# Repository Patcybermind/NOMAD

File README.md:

# NOMAD
A laptop designed to be customisable, portable and open source

if you're in the hc slack make sure to join #pats-basement

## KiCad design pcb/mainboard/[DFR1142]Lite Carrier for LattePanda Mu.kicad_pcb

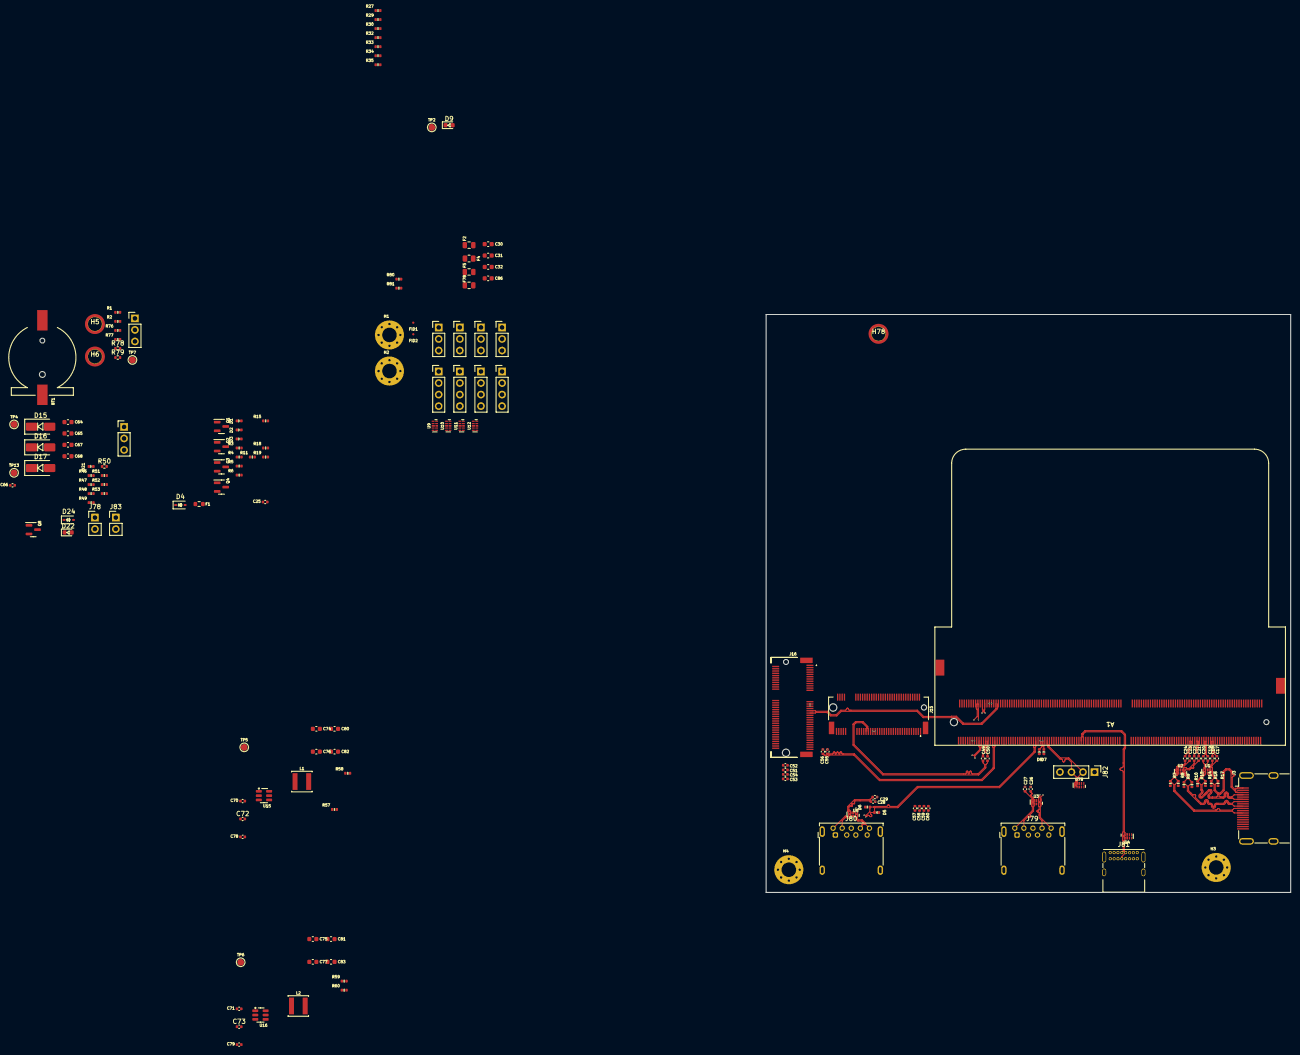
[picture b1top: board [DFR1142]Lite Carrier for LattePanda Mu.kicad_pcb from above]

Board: 4 copper layers, 115.5 x 127.2 mm, 166 parts (0 on the bottom side), 130 nets.

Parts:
A1: LattePanda_Mu; LattePanda_Module_H8.0mm_Horizontal
BT1: Battery_Cell; Battery_Holder_CR1220_S8411-45R
C17, C18, C19, C20, C21, C22, C23, C24, C25, C26, C27, C28, C29, C52, C54, C58, C60, C70, C71, C78, C79: 100nF/50V; C_0402_1005Metric
C30, C31, C32, C64, C65, C67, C68, C74, C75, C76, C77, C80, C81, C82, C83, C86: 22uF/10V; C_0603_1608Metric
C49, C50, C55, C56: 220nF/50V; C_0402_1005Metric
C51, C53, C57, C59: 10uF/10V; C_0402_1005Metric
C66: 1uF/16V; C_0402_1005Metric
C72, C73: 12pF/50V; C_0402_1005Metric
D1, D2, D3, D5, D6, D7, D8, D21: ESD5V0B03; D_0402_1005Metric
D4: 1N5819WS; D_SOD-323
D9, D22: LED_G; LED_0603_1608Metric
D15, D16, D17: SS54; D_SMA
D24: 3V3 Izt=5mA; D_SOD-323
F1: 6V/50mA; R_0603_1608Metric
F2, F78: 6V/1A; Fuse_0805_2012Metric
F4: 6V/2A; R_0805_2012Metric
F5: 6V/2A; Fuse_0805_2012Metric
FID1, FID2: Fiducial; Fiducial_0.5mm_Mask1mm
H1, H2, H3, H4: MountingHole_Pad; MountingHole_3.2mm_M3_Pad_Via
H5, H6, H78: MountingHole_Pad; MountingHole_3mm_M2_Pad_TopOnly
J1, J8, J10, J11, J14: Conn_01x03_Pin; PinHeader_1x03_P2.54mm_Vertical
J3: HDMI_A; HDMI_A_Molex_208658-1001_Horizontal
J7, J9, J12, J13, J82: Conn_01x04_Pin; PinHeader_1x04_P2.54mm_Vertical
J15: Bus_M.2_Socket_M; PCIe_M.2_Connectors_P=0.5mm_H=4.2mm_KeyM
J16: Bus_M.2_Socket_E; PCIe_M.2_Connectors_P=0.5mm_H=4.2mm_KeyE
J78, J83: Conn_01x02_Pin; PinHeader_1x02_P2.54mm_Vertical
J79, J80: USB3_A; USB3_A_Molex_48393-001
J81: USB_C_Receptacle_USB2.0_16P; USB_C_Receptacle_GCT_USB4085
JP1: Jumper_3_Bridged12; PinHeader_1x03_P2.54mm_Vertical
L1, L2: 2.2uH/4.3A; L_Sunlord_SWPA4020S
Q1, Q8: 2N7002; SOT-23
Q2, Q3, Q4: 2SK3018; SOT-23
R1, R11, R47: 1K/1%; R_0402_1005Metric
R2, R34, R35, R49, R50, R58, R78, R79: 10K/1%; R_0402_1005Metric
R3, R5, R15, R18, R19, R30, R52, R53: 2.2K/1%; R_0402_1005Metric
R4: 1M/1%; R_0402_1005Metric
R6, R59: 21.5K/1%; R_0402_1005Metric
R7, R8, R9, R10, R13, R14, R16, R17: 470R/1%; R_0402_1005Metric
R27, R29, R32, R33: 0R/1%; R_0402_1005Metric
R46, R48: 100R/1%; R_0402_1005Metric
R51, R76, R77: 100K/1%; R_0402_1005Metric
R57: 75K/1%; R_0402_1005Metric
R60: 4.7K/1%; R_0402_1005Metric
R80, R81: 5.1K/1%; R_0402_1005Metric
TP2, TP4, TP5, TP6, TP7, TP13: TestPoint; TestPoint_Pad_D1.5mm
U1, U2: TPAZ1023-04F; Diodes_UDFN-10_1.0x2.5mm_P0.5mm
U3, U4, U5, U9, U10, U11, U12, U78: ULC0524P; Diodes_UDFN-10_1.0x2.5mm_P0.5mm
U15, U16: SY8253ADC; TSOT-23-6

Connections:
5V_HDMI_VCC: C25.1, D4.1 (K), F1.1, R15.1, R18.1
+3V3: C51.2, C52.2, C53.2, C54.2, C57.2, C58.2, C59.2, C60.2, C73.1, C75.2, C77.2, C79.1, C81.2, C83.2, J13.1, J13.2, J13.3, J13.4, J14.1, J14.2, J14.3, J15.2 (3.3V), J15.4 (3.3V), J15.12 (3.3V), J15.14 (3.3V), J15.16 (3.3V), J15.18 (3.3V), J15.70 (3.3V), J15.72 (3.3V), J15.74 (3.3V), J16.2 (3.3V), J16.4 (3.3V), J16.72 (3.3V), J16.74 (3.3V), L2.2, Q1.1 (G), Q2.1 (G), Q3.1 (G), R3.1, R4.1, R5.1, R30.2, R34.2, R35.1, R50.2, R52.2, R59.2, TP6.1
+5V: C30.2, C31.2, C32.2, C72.1, C74.2, C76.2, C78.1, C80.2, C82.2, C86.2, D4.2 (A), F2.1, F4.1, F5.1, F78.1, L1.2, R57.2, TP5.1
+12V: D15.2 (A), D16.2 (A), D17.2 (A), J78.1, TP4.1
+BATT: A1.115 (VBAT), R1.1
/GPIO/I2C2_SCL: A1.154 (I2C2_SCL), J9.1, U11.1, U11.10 (NC)
/GPIO/I2C2_SDA: A1.156 (I2C2_SDA), J7.1, U9.1, U9.10 (NC)
/GPIO/I2C3_SCL: A1.150 (I2C3_SCL), J9.2, U11.2, U11.9 (NC)
/GPIO/I2C3_SDA: A1.152 (I2C3_SDA), J7.2, U9.2, U9.9 (NC)
/GPIO/I2C4_SCL: A1.146 (I2C4_SCL), J9.3, U11.4, U11.7 (NC)
/GPIO/I2C4_SDA: A1.148 (I2C4_SDA), J7.3, U9.4, U9.7 (NC)
/GPIO/I2C5_SCL: A1.142 (I2C5_SCL), J9.4, U11.5, U11.6 (NC)
/GPIO/I2C5_SDA: A1.144 (I2C5_SDA), J7.4, U9.5, U9.6 (NC)
/GPIO/SOC_UART0_RX: A1.137 (UART0_RXD), J8.1, U10.1, U10.10 (NC)
/GPIO/SOC_UART0_TX: A1.139 (UART0_TXD), J10.1, U12.1, U12.10 (NC)
/GPIO/SOC_UART1_RX: A1.141 (UART1_RXD), J8.2, U10.2, U10.9 (NC)
/GPIO/SOC_UART1_TX: A1.143 (UART1_TXD), J10.2, U12.2, U12.9 (NC)
/GPIO/SOC_UART2_RX: A1.140 (UART2_RXD), J8.3, U10.4, U10.7 (NC)
/GPIO/SOC_UART2_TX: A1.138 (UART2_TXD), J10.3, U12.4, U12.7 (NC)
/HDMI/DDC_SCL: D1.2 (A2), J3.15 (SCL), Q2.3 (D), R15.2
/HDMI/DDC_SDA: D3.2 (A2), J3.16 (SDA), Q3.3 (D), R18.2
/HDMI/DDI_B_DDC_SCL: A1.171 (DDIB_DDC_SCL), Q2.2 (S), R5.2
/HDMI/DDI_B_DDC_SDA: A1.169 (DDIB_DDC_SDA), Q3.2 (S), R3.2
/HDMI/DDI_B_HPD: A1.183 (DDIB_HPD), Q1.2 (S), R4.2
/HDMI/DDI_B_TX0+: A1.217 (DDIB_TX0+), C17.1
/HDMI/DDI_B_TX0-: A1.215 (DDIB_TX0-), C18.1
/HDMI/DDI_B_TX1+: A1.211 (DDIB_TX1+), C19.1
/HDMI/DDI_B_TX1-: A1.209 (DDIB_TX1-), C20.1
/HDMI/DDI_B_TX2+: A1.205 (DDIB_TX2+), C21.1
/HDMI/DDI_B_TX2-: A1.203 (DDIB_TX2-), C22.1
/HDMI/DDI_B_TX3+: A1.199 (DDIB_TX3+), C23.1
/HDMI/DDI_B_TX3-: A1.197 (DDIB_TX3-), C24.1
/HDMI/HPD: D2.2 (A2), J3.19 (HPD), R11.2
/HDMI/TMDS_CK+: C23.2, J3.10 (CK+), R8.1, U2.4, U2.7 (NC)
/HDMI/TMDS_CK-: C24.2, J3.12 (CK-), R7.1, U2.5, U2.6 (NC)
/HDMI/TMDS_D0+: C21.2, J3.7 (D0+), R10.1, U2.1, U2.10 (NC)
/HDMI/TMDS_D0-: C22.2, J3.9 (D0-), R9.1, U2.2, U2.9 (NC)
/HDMI/TMDS_D1+: C19.2, J3.4 (D1+), R14.1, U1.4, U1.7 (NC)
/HDMI/TMDS_D1-: C20.2, J3.6 (D1-), R13.1, U1.5, U1.6 (NC)
/HDMI/TMDS_D2+: C17.2, J3.1 (D2+), R17.1, U1.1, U1.10 (NC)
/HDMI/TMDS_D2-: C18.2, J3.3 (D2-), R16.1, U1.2, U1.9 (NC)
/LattePanda Module/HSIO_0_TX+: A1.13 (HSIO0_TX+), C27.1
/LattePanda Module/HSIO_0_TX-: A1.15 (HSIO0_TX-), C26.1
/LattePanda Module/HSIO_1_TX+: A1.19 (HSIO1_TX+), C29.1
/LattePanda Module/HSIO_1_TX-: A1.21 (HSIO1_TX-), C28.1
/LattePanda Module/HSIO_2_RX+: A1.28 (HSIO2_RX+), J15.43 (PERp0/SATA-B-)
/LattePanda Module/HSIO_2_RX-: A1.30 (HSIO2_RX-), J15.41 (PERn0/SATA-B+)
/LattePanda Module/HSIO_2_TX+: A1.25 (HSIO2_TX+), C49.1
/LattePanda Module/HSIO_2_TX-: A1.27 (HSIO2_TX-), C50.1
/LattePanda Module/HSIO_3_RX+: A1.34 (HSIO3_RX+), J16.41 (PERp0)
/LattePanda Module/HSIO_3_RX-: A1.36 (HSIO3_RX-), J16.43 (PERn0)
/LattePanda Module/HSIO_3_TX+: A1.31 (HSIO3_TX+), C55.1
/LattePanda Module/HSIO_3_TX-: A1.33 (HSIO3_TX-), C56.1
/LattePanda Module/REFCLK0+: A1.85 (REFCLK0+), J15.53 (REFCLKn)
/LattePanda Module/REFCLK0-: A1.87 (REFCLK0-), J15.55 (REFCLKp)
/LattePanda Module/REFCLK3+: A1.88 (REFCLK3+), J16.47 (REFCLKp0)
/LattePanda Module/REFCLK3-: A1.90 (REFCLK3-), J16.49 (REFCLKn0)
/LattePanda Module/SLS_S3: A1.7 (SLS_S3), JP1.3 (B)
/LattePanda Module/SUSCLK_WIFI: A1.131 (SUSCLK), R29.2, R33.2
/LattePanda Module/USB_2_P7+: A1.76 (USB2_P7+), J16.3 (USB_D+)
/LattePanda Module/USB_2_P7-: A1.78 (USB2_P7-), J16.5 (USB_D-)
/LattePanda Module/~PWR_SW: A1.1 (~PWRBTN), R48.2
/M.2 E&M Key/CON_PCIE_TX_0+: C55.2, J16.35 (PETp0)
/M.2 E&M Key/CON_PCIE_TX_0-: C56.2, J16.37 (PETn0)
/M.2 E&M Key/CON_PCIE_TX_1+: C49.2, J15.49 (PETp0/SATA-A+)
/M.2 E&M Key/CON_PCIE_TX_1-: C50.2, J15.47 (PETn0/SATA-A-)
/M.2 E&M Key/~CLKREQE: J16.53 (~CLKREQ0), R32.1
/M.2 E&M Key/~CLKREQM: J15.52 (~CLKREQ), R27.1
/PSU/PWR_EN: R46.2, R51.2, U15.4 (EN), U16.4 (EN)
/USB2.0&USB3.0/CON_USB1_D_N: A1.109 (USB2_P5-), J81.A7 (D-), J81.B7 (D-), U4.2, U4.9 (NC)
/USB2.0&USB3.0/CON_USB1_D_P: A1.111 (USB2_P5+), J81.A6 (D+), J81.B6 (D+), U4.1, U4.10 (NC)
/USB2.0&USB3.0/CON_USB2_D_N: A1.79 (USB2_P3-), J82.3, U78.5, U78.6 (NC)
/USB2.0&USB3.0/CON_USB2_D_P: A1.81 (USB2_P3+), J82.2, U78.4, U78.7 (NC)
/USB2.0&USB3.0/CON_USB3_D_N: A1.73 (USB2_P2-), D8.2 (A2), J79.2 (D-)
/USB2.0&USB3.0/CON_USB3_D_P: A1.75 (USB2_P2+), D7.2 (A2), J79.3 (D+)
/USB2.0&USB3.0/CON_USB3_SSRX_N: A1.18 (HSIO0_RX-), J79.5 (SSRX-), U3.1, U3.10 (NC)
/USB2.0&USB3.0/CON_USB3_SSRX_P: A1.16 (HSIO0_RX+), J79.6 (SSRX+), U3.2, U3.9 (NC)
/USB2.0&USB3.0/CON_USB3_SSTX_N: C26.2, J79.8 (SSTX-), U3.4, U3.7 (NC)
/USB2.0&USB3.0/CON_USB3_SSTX_P: C27.2, J79.9 (SSTX+), U3.5, U3.6 (NC)
/USB2.0&USB3.0/CON_USB4_D_N: A1.67 (USB2_P1-), D6.2 (A2), J80.2 (D-)
/USB2.0&USB3.0/CON_USB4_D_P: A1.69 (USB2_P1+), D5.2 (A2), J80.3 (D+)
/USB2.0&USB3.0/CON_USB4_SSRX_N: A1.24 (HSIO1_RX-), J80.5 (SSRX-), U5.1, U5.10 (NC)
/USB2.0&USB3.0/CON_USB4_SSRX_P: A1.22 (HSIO1_RX+), J80.6 (SSRX+), U5.2, U5.9 (NC)
/USB2.0&USB3.0/CON_USB4_SSTX_N: C28.2, J80.8 (SSTX-), U5.4, U5.7 (NC)
/USB2.0&USB3.0/CON_USB4_SSTX_P: C29.2, J80.9 (SSTX+), U5.5, U5.6 (NC)
/~PLT_RST: A1.105 (~PLTRST), J15.50 (~PERST), J16.52 (~PERST0)
/~PWR_LED/~PSON: A1.5 (SLS_S0), JP1.1 (A), R19.1, R47.1
/~WAKE: A1.103 (~WAKE), J15.54 (~PEWAKE), J16.55 (~PEWAKE0)
GND: A1.11 (GND), A1.14 (GND), A1.17 (GND), A1.20 (GND), A1.23 (GND), A1.26 (GND), A1.29 (GND), A1.32 (GND), A1.35 (GND), A1.38 (GND), A1.41 (GND), A1.44 (GND), A1.47 (GND), A1.50 (GND), A1.53 (GND), A1.56 (GND), A1.59 (GND), A1.62 (GND), A1.65 (GND), A1.68 (GND), A1.71 (GND), A1.74 (GND), A1.77 (GND), A1.80 (GND), A1.83 (GND), A1.86 (GND), A1.89 (GND), A1.92 (GND), A1.95 (GND), A1.98 (GND), A1.101 (GND), A1.107 (GND), A1.110 (GND), A1.113 (GND), A1.116 (GND), A1.135 (GND), A1.136 (GND), A1.151 (GND), A1.158 (GND), A1.167 (GND), A1.170 (GND), A1.181 (GND), A1.182 (GND), A1.188 (GND), A1.189 (GND), A1.194 (GND), A1.195 (GND), A1.200 (GND), A1.201 (GND), A1.206 (GND), A1.207 (GND), A1.212 (GND), A1.213 (GND), A1.218 (GND), A1.219 (GND), A1.224 (GND), A1.225 (GND), A1.230 (GND), A1.231 (GND), A1.236 (GND), A1.237 (GND), A1.242 (GND), A1.243 (GND), A1.248 (GND), A1.249 (GND), A1.MP (Mountinge_Pads), BT1.2 (-), C25.2, C30.1, C31.1, C32.1, C51.1, C52.1, C53.1, C54.1, C57.1, C58.1, C59.1, C60.1, C64.1, C65.1, C66.2, C67.1, C68.1, C74.1, C75.1, C76.1, C77.1, C78.2, C79.2, C80.1, C81.1, C82.1, C83.1, C86.1, D1.1 (A1), D2.1 (A1), D3.1 (A1), D5.1 (A1), D6.1 (A1), D7.1 (A1), D8.1 (A1), D21.1 (A1), D24.2 (A), H1.1, H2.1, H3.1, H4.1, H5.1, H6.1, J1.3, J3.2 (D2S), J3.5 (D1S), J3.8 (D0S), J3.11 (CKS), J3.17 (GND), J3.SH, J11.1, J11.2, J11.3, J12.1, J12.2, J12.3, J12.4, J15.1 (GND), J15.3 (GND), J15.9 (GND), J15.15 (GND), J15.21 (GND), J15.27 (GND), J15.33 (GND), J15.39 (GND), J15.45 (GND), J15.51 (GND), J15.57 (GND), J15.71 (GND), J15.73 (GND), J15.75 (GND), J15.MP1, J15.MP2, J16.1 (GND), J16.7 (GND), J16.18 (GND), J16.33 (GND), J16.39 (GND), J16.45 (GND), J16.51 (GND), J16.57 (GND), J16.63 (GND), J16.69 (GND), J16.75 (GND), J16.MP1, J16.MP2, J78.2, J79.4 (GND), J79.7 (DRAIN), J79.10 (SHIELD), J80.4 (GND), J80.7 (DRAIN), J80.10 (SHIELD), J81.A1 (GND), J81.A12 (GND), J81.B1 (GND), J81.B12 (GND), J81.S1 (SHIELD), J82.4, J83.1, Q4.2 (S), Q8.2 (S), R6.2, R27.2, R32.2, R49.1, R51.1, R58.1, R60.1, R76.2, R77.2, R78.2, R79.2, U1.3 (VSS), U1.8 (VSS), U2.3 (VSS), U2.8 (VSS), U3.3 (VSS), U3.8 (VSS), U4.3 (VSS), U4.8 (VSS), U5.3 (VSS), U5.8 (VSS), U9.3 (VSS), U9.8 (VSS), U10.3 (VSS), U10.8 (VSS), U11.3 (VSS), U11.8 (VSS), U12.3 (VSS), U12.8 (VSS), U15.2 (GND), U16.2 (GND)
unnamed: A1.12 (SIO_UART_RX), J1.2
unnamed: A1.10 (SIO_UART_TX), J1.1
unnamed: A1.187 (TCP0_HPD), R76.1
unnamed: A1.185 (TCP1_HPD), R77.1
unnamed: A1.133 (~BIOS_SEL), R2.1, TP7.1
unnamed: A1.100 (~CLKREQ3), R79.1
unnamed: A1.102 (~CLKREQ4), R78.1
unnamed: BT1.1 (+), R1.2
unnamed: D9.2 (A), R30.1
unnamed: D9.1 (K), J15.10 (DAS/~DSS/~LED1)
unnamed: C66.1, D21.2 (A2), J83.2, R48.1, R50.1
unnamed: D22.2 (A), R52.1
unnamed: D22.1 (K), Q8.3 (D)
unnamed: F2.2, J81.A4 (VBUS), J81.A9 (VBUS), J81.B4 (VBUS), J81.B9 (VBUS), R80.1, R81.1
unnamed: F1.2, J3.18 (+5V)
unnamed: J15.38 (DEVSLP), TP2.1
unnamed: J15.68 (SUSCLK), R29.1
unnamed: J16.50 (SUSCLK), R33.1
unnamed: J16.56 (~W_DISABLE1), R34.1
unnamed: J16.54 (~W_DISABLE2), R35.2
unnamed: F4.2, J79.1 (VBUS)
unnamed: F5.2, J80.1 (VBUS)
unnamed: J81.A5 (CC1), R80.2
unnamed: J81.B5 (CC2), R81.2
unnamed: F78.2, J82.1
unnamed: JP1.2 (C), R46.1
unnamed: Q1.3 (D), R6.1, R11.1
unnamed: Q4.3 (D), R7.2, R8.2, R9.2, R10.2, R13.2, R14.2, R16.2, R17.2
unnamed: Q4.1 (G), R19.2
unnamed: Q8.1 (G), R47.2, R49.2
unnamed: U10.5, U10.6 (NC)
unnamed: U12.5, U12.6 (NC)
unnamed: C70.2, U15.1 (BOOST)
unnamed: C72.2, R57.1, R58.2, U15.3 (FB)
unnamed: C70.1, L1.1, U15.6 (SW)
unnamed: C71.2, U16.1 (BOOST)
unnamed: C73.2, R59.1, R60.2, U16.3 (FB)
unnamed: C71.1, L2.1, U16.6 (SW)
unnamed: U78.3 (VSS), U78.8 (VSS)
VDC: A1.250 (VIN), A1.251 (VIN), A1.252 (VIN), A1.253 (VIN), A1.254 (VIN), A1.255 (VIN), A1.256 (VIN), A1.257 (VIN), A1.258 (VIN), A1.259 (VIN), A1.260 (VIN), C64.2, C65.2, C67.2, C68.2, D15.1 (K), D16.1 (K), D17.1 (K), R53.1, U15.5 (VIN), U16.5 (VIN)
VPullup: D24.1 (K), R2.2, R53.2, TP13.1

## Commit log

2025-06-30 explained some more
2025-07-07 added pcb files
2025-07-08 mainboard schematic done
2025-07-10 before i start jul 10th
2025-07-11 ready for routing
2025-07-11 before sleep
2025-07-11 board setup for 90 ohms and 10ohms ready and netclass assignmetnnts left to default
2025-07-11 made ttracks smaller in netclass setings
2025-07-11 added extra esd to schem but not pcb also routed differential pairs of hdmi
2025-07-11 gtg leave
2025-07-18 restarted board hdmi done
2025-07-18 started high speed traces on l3
2025-07-18 a lot has been routed
2025-07-18 latest
2025-07-18 gtg sleep
2025-07-19 most length matching almost done
